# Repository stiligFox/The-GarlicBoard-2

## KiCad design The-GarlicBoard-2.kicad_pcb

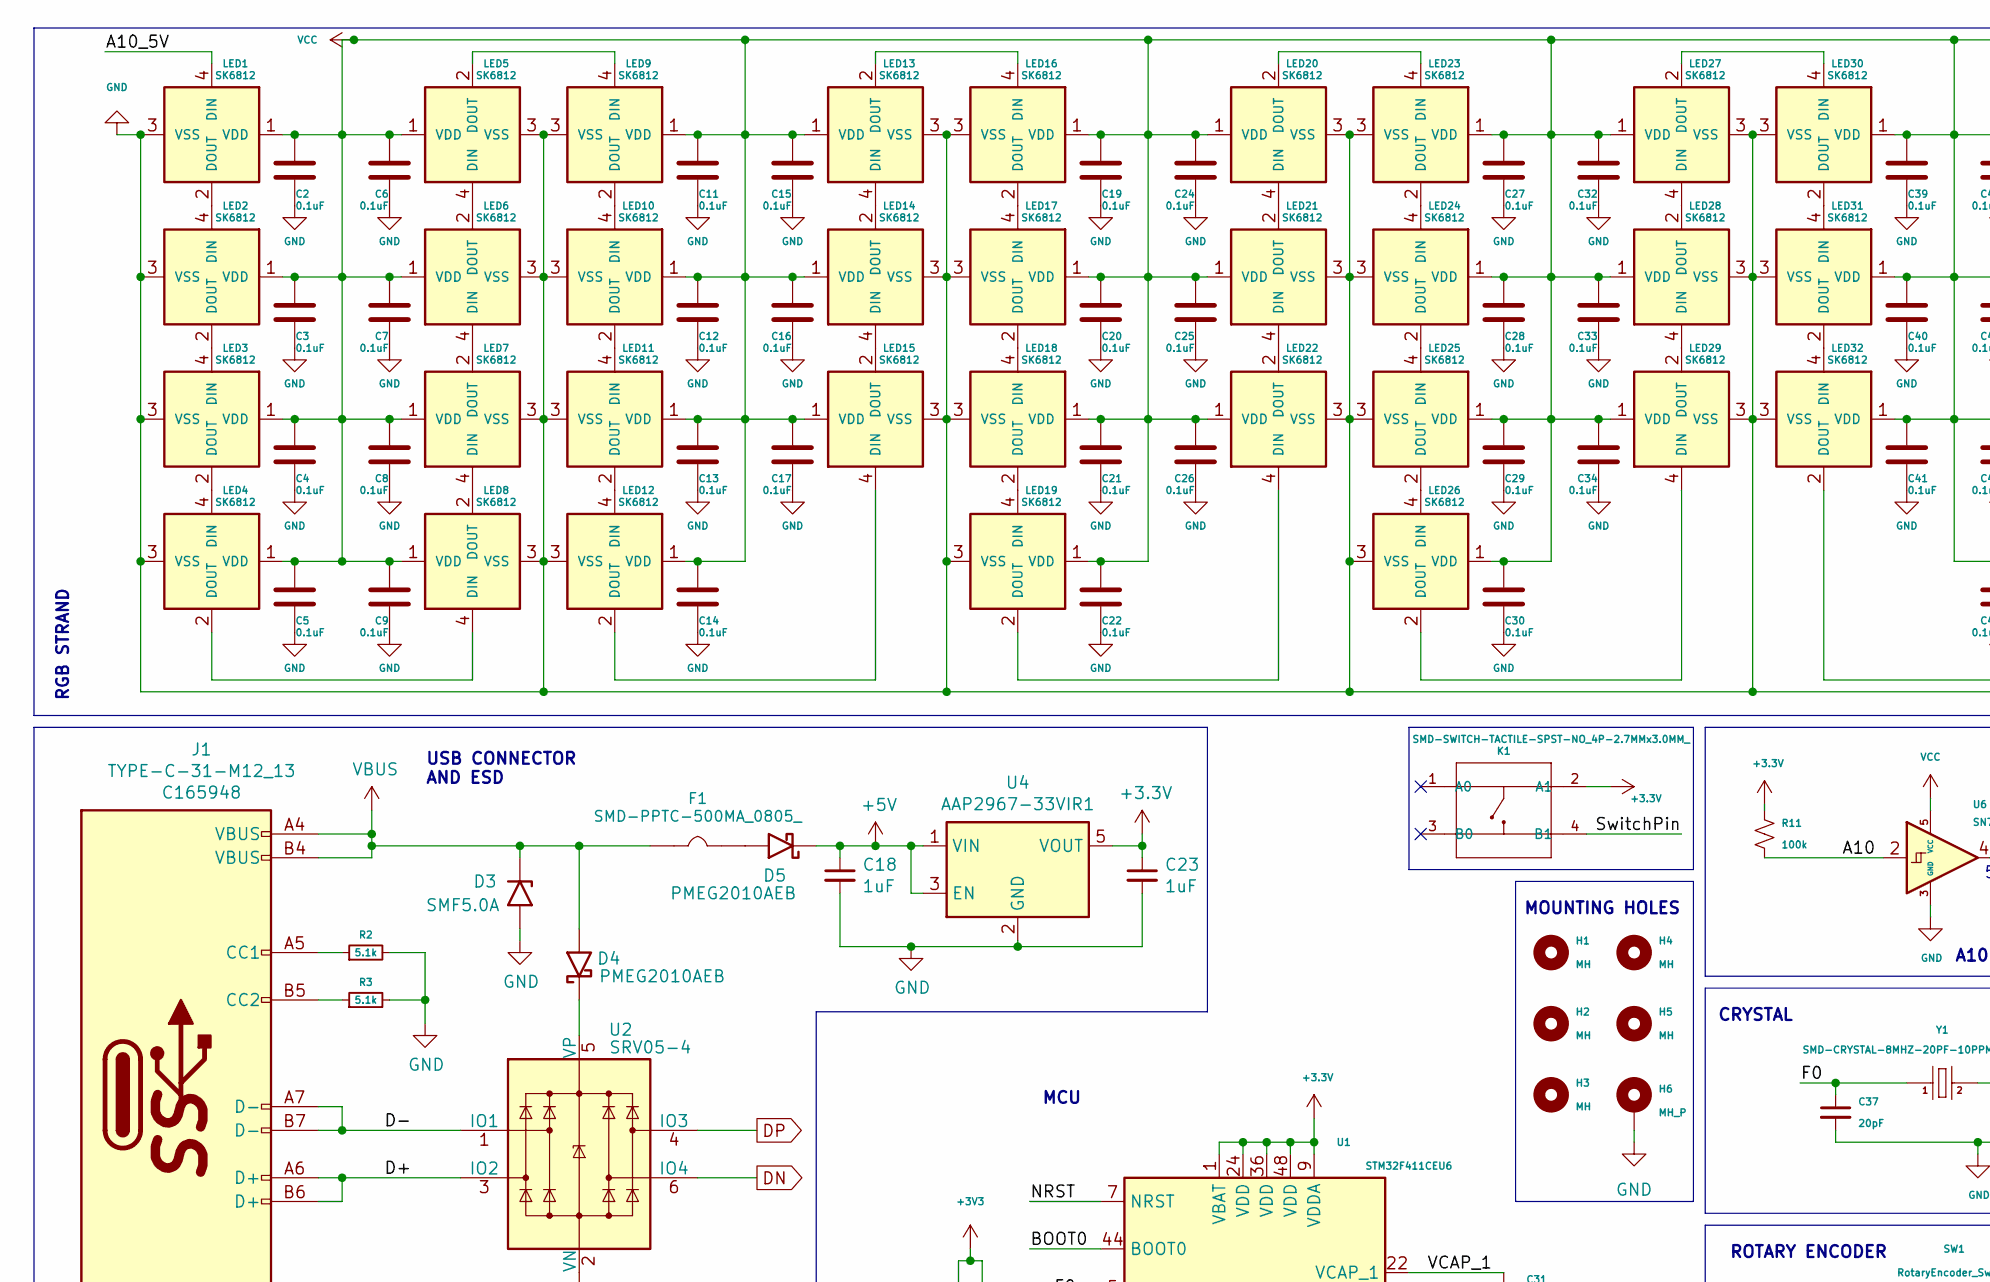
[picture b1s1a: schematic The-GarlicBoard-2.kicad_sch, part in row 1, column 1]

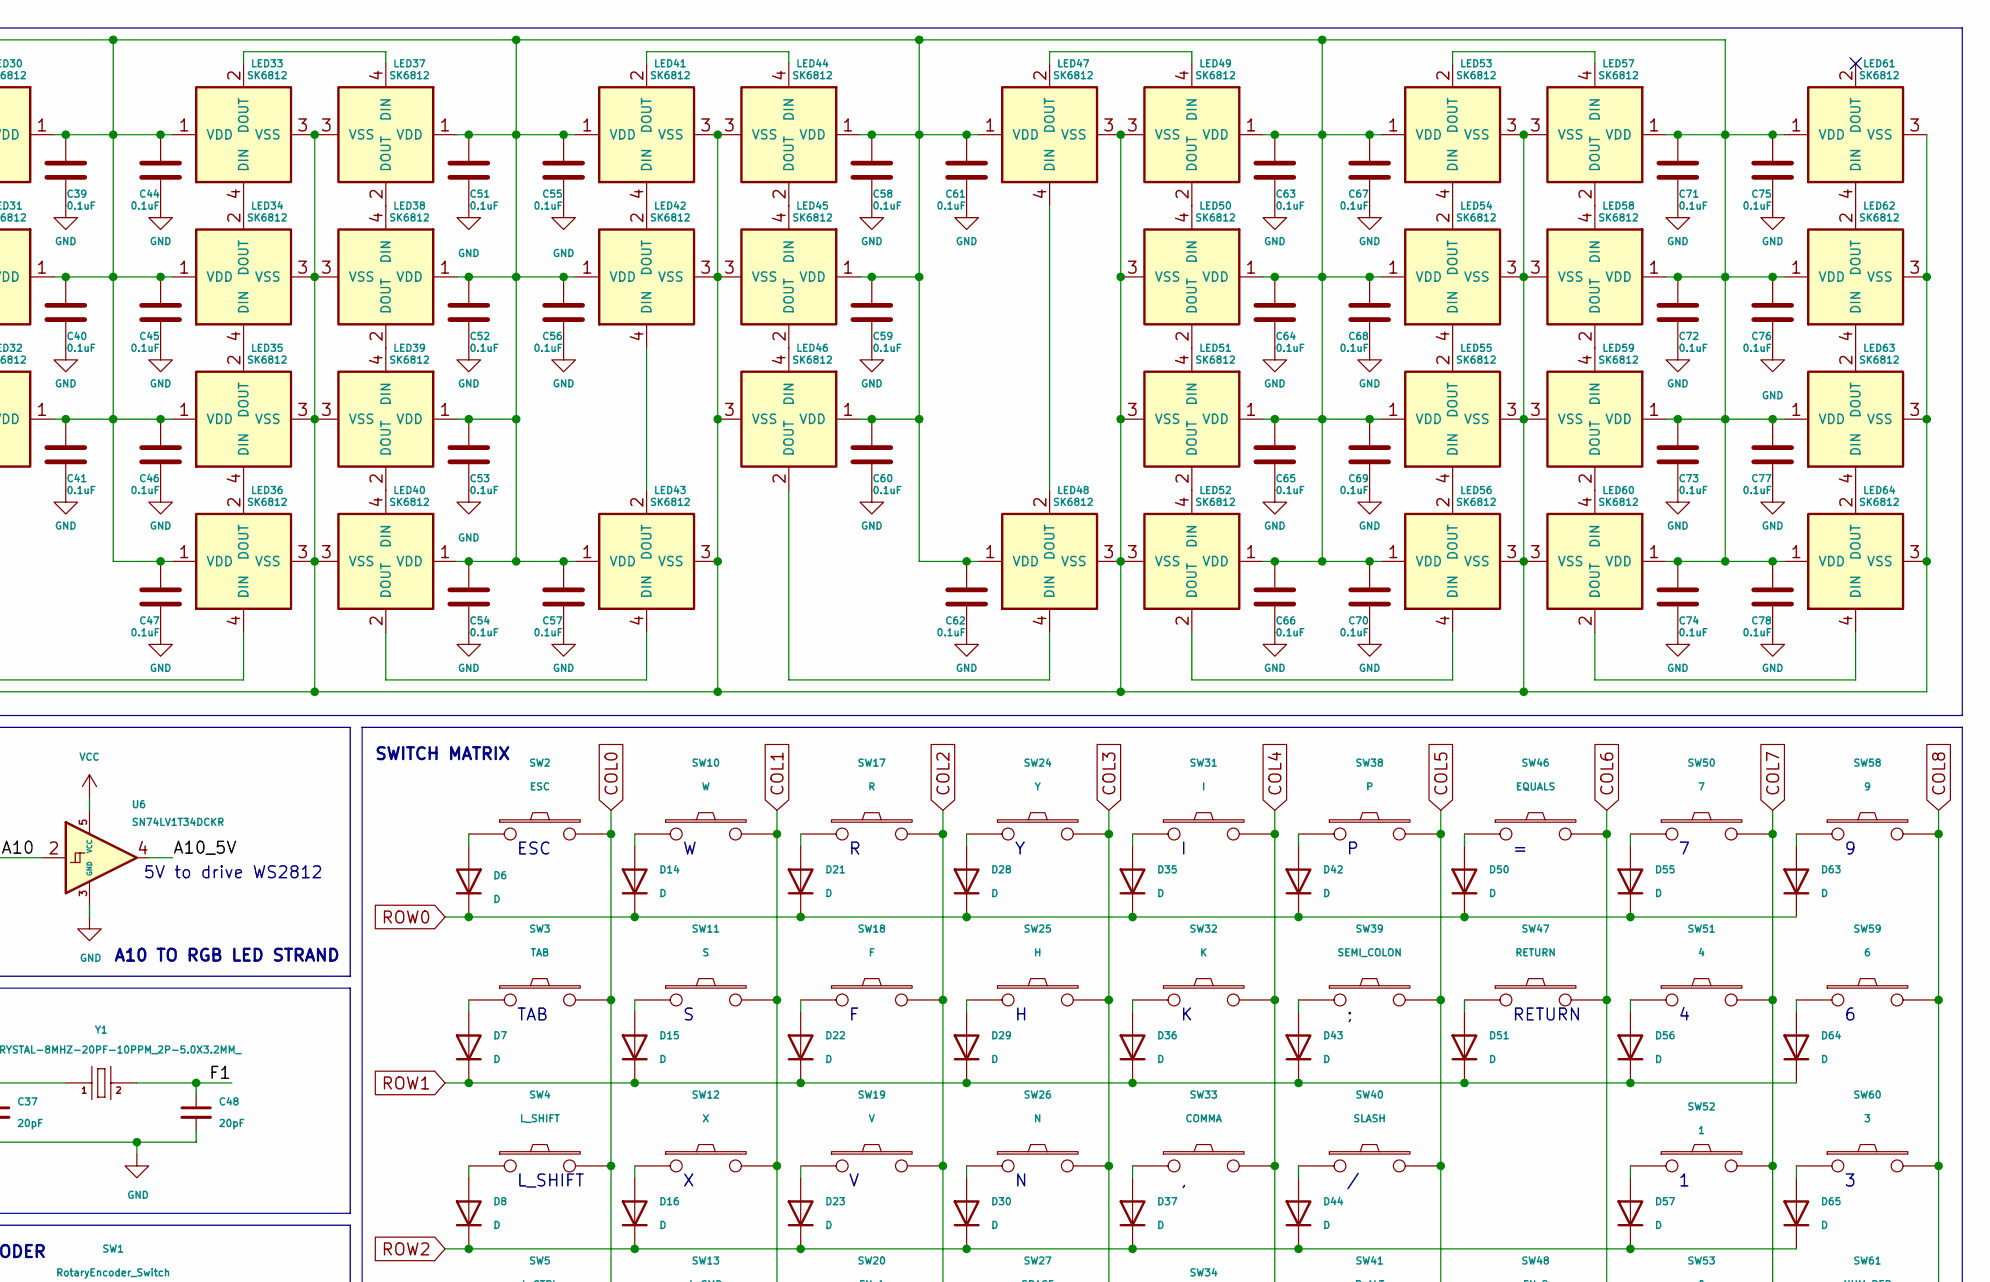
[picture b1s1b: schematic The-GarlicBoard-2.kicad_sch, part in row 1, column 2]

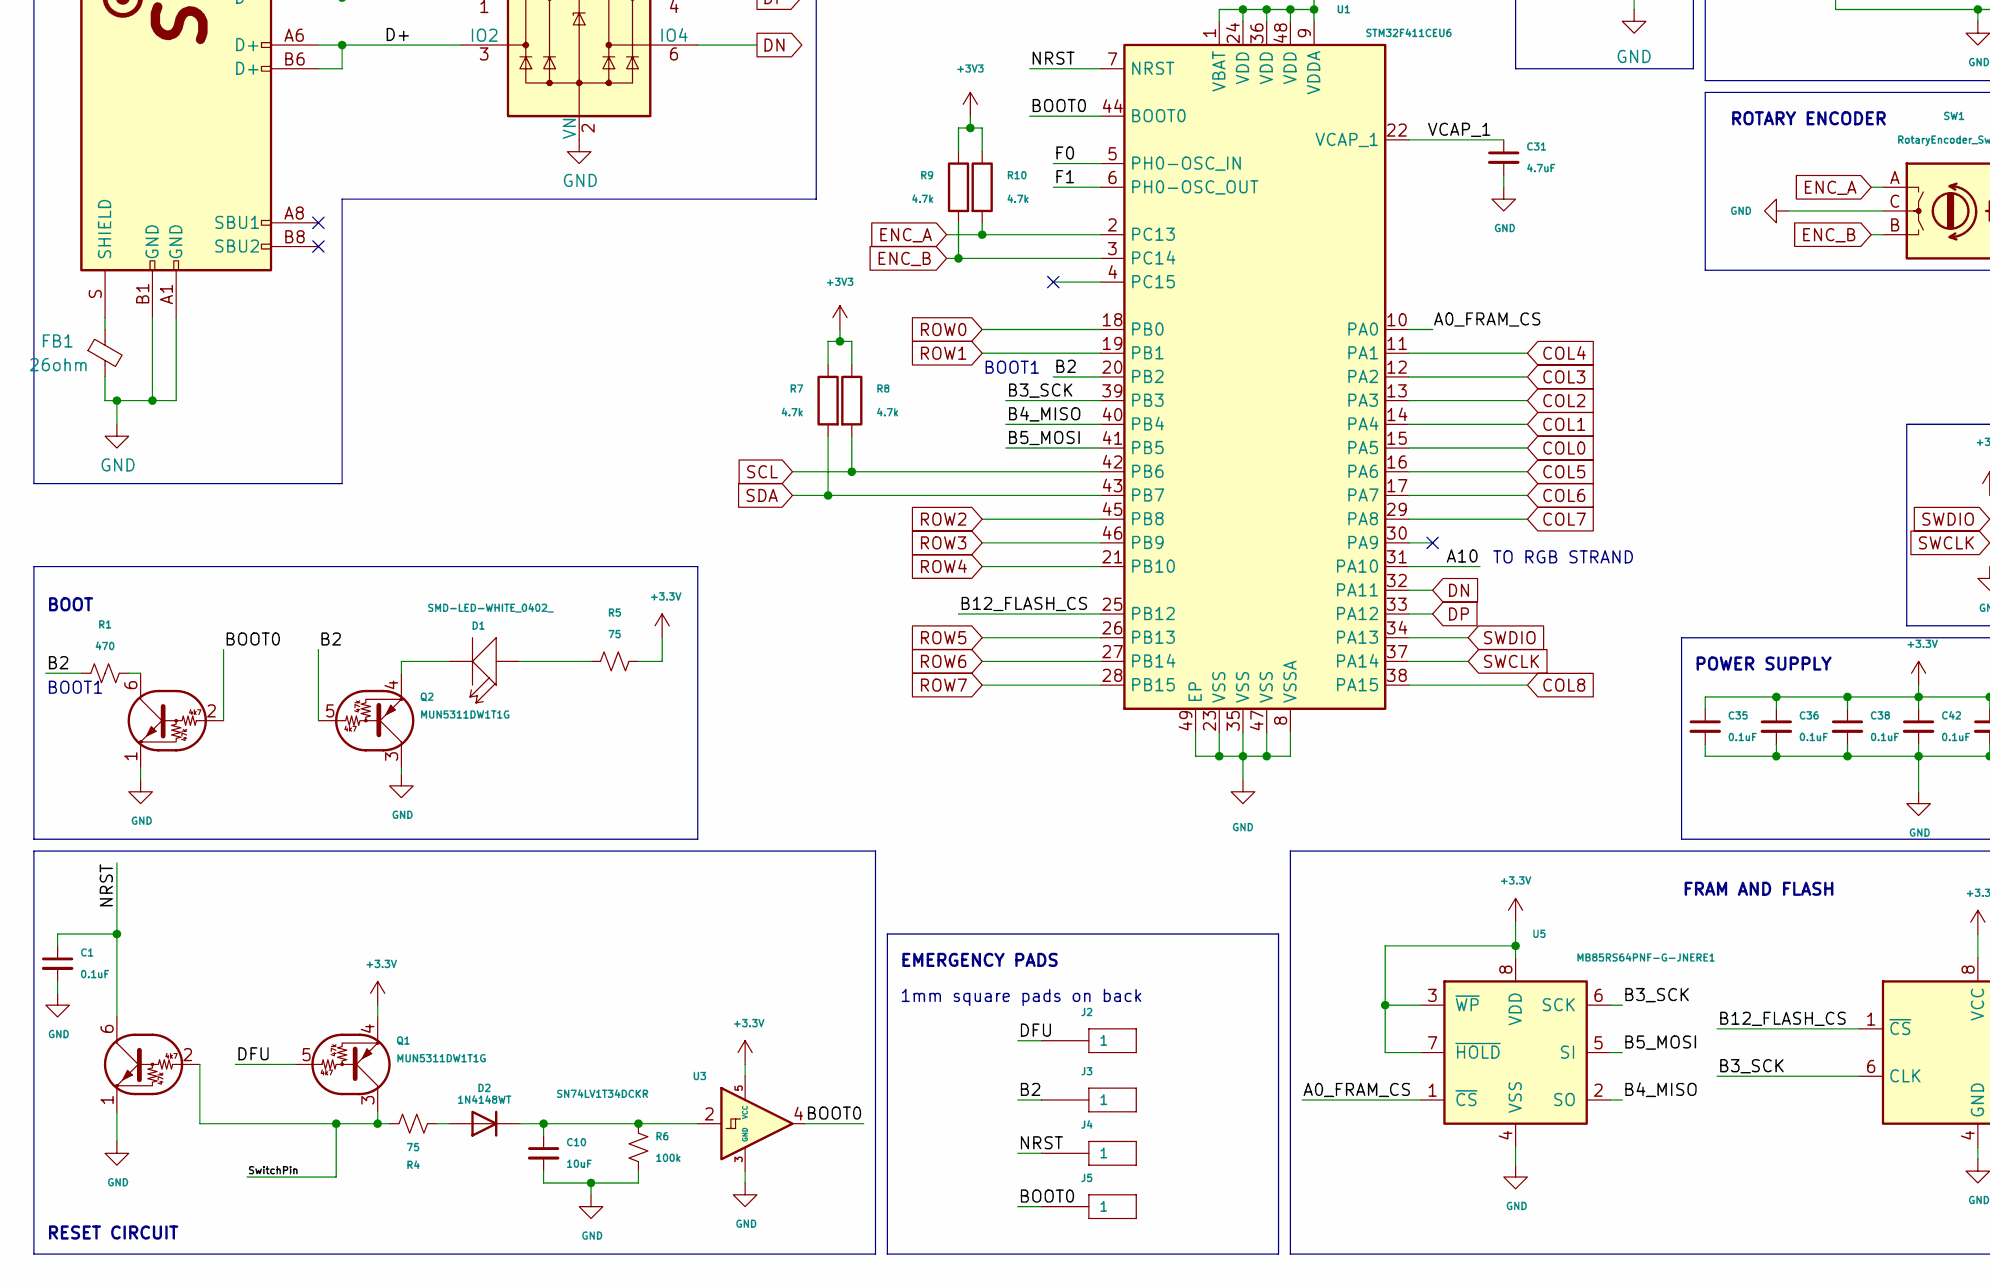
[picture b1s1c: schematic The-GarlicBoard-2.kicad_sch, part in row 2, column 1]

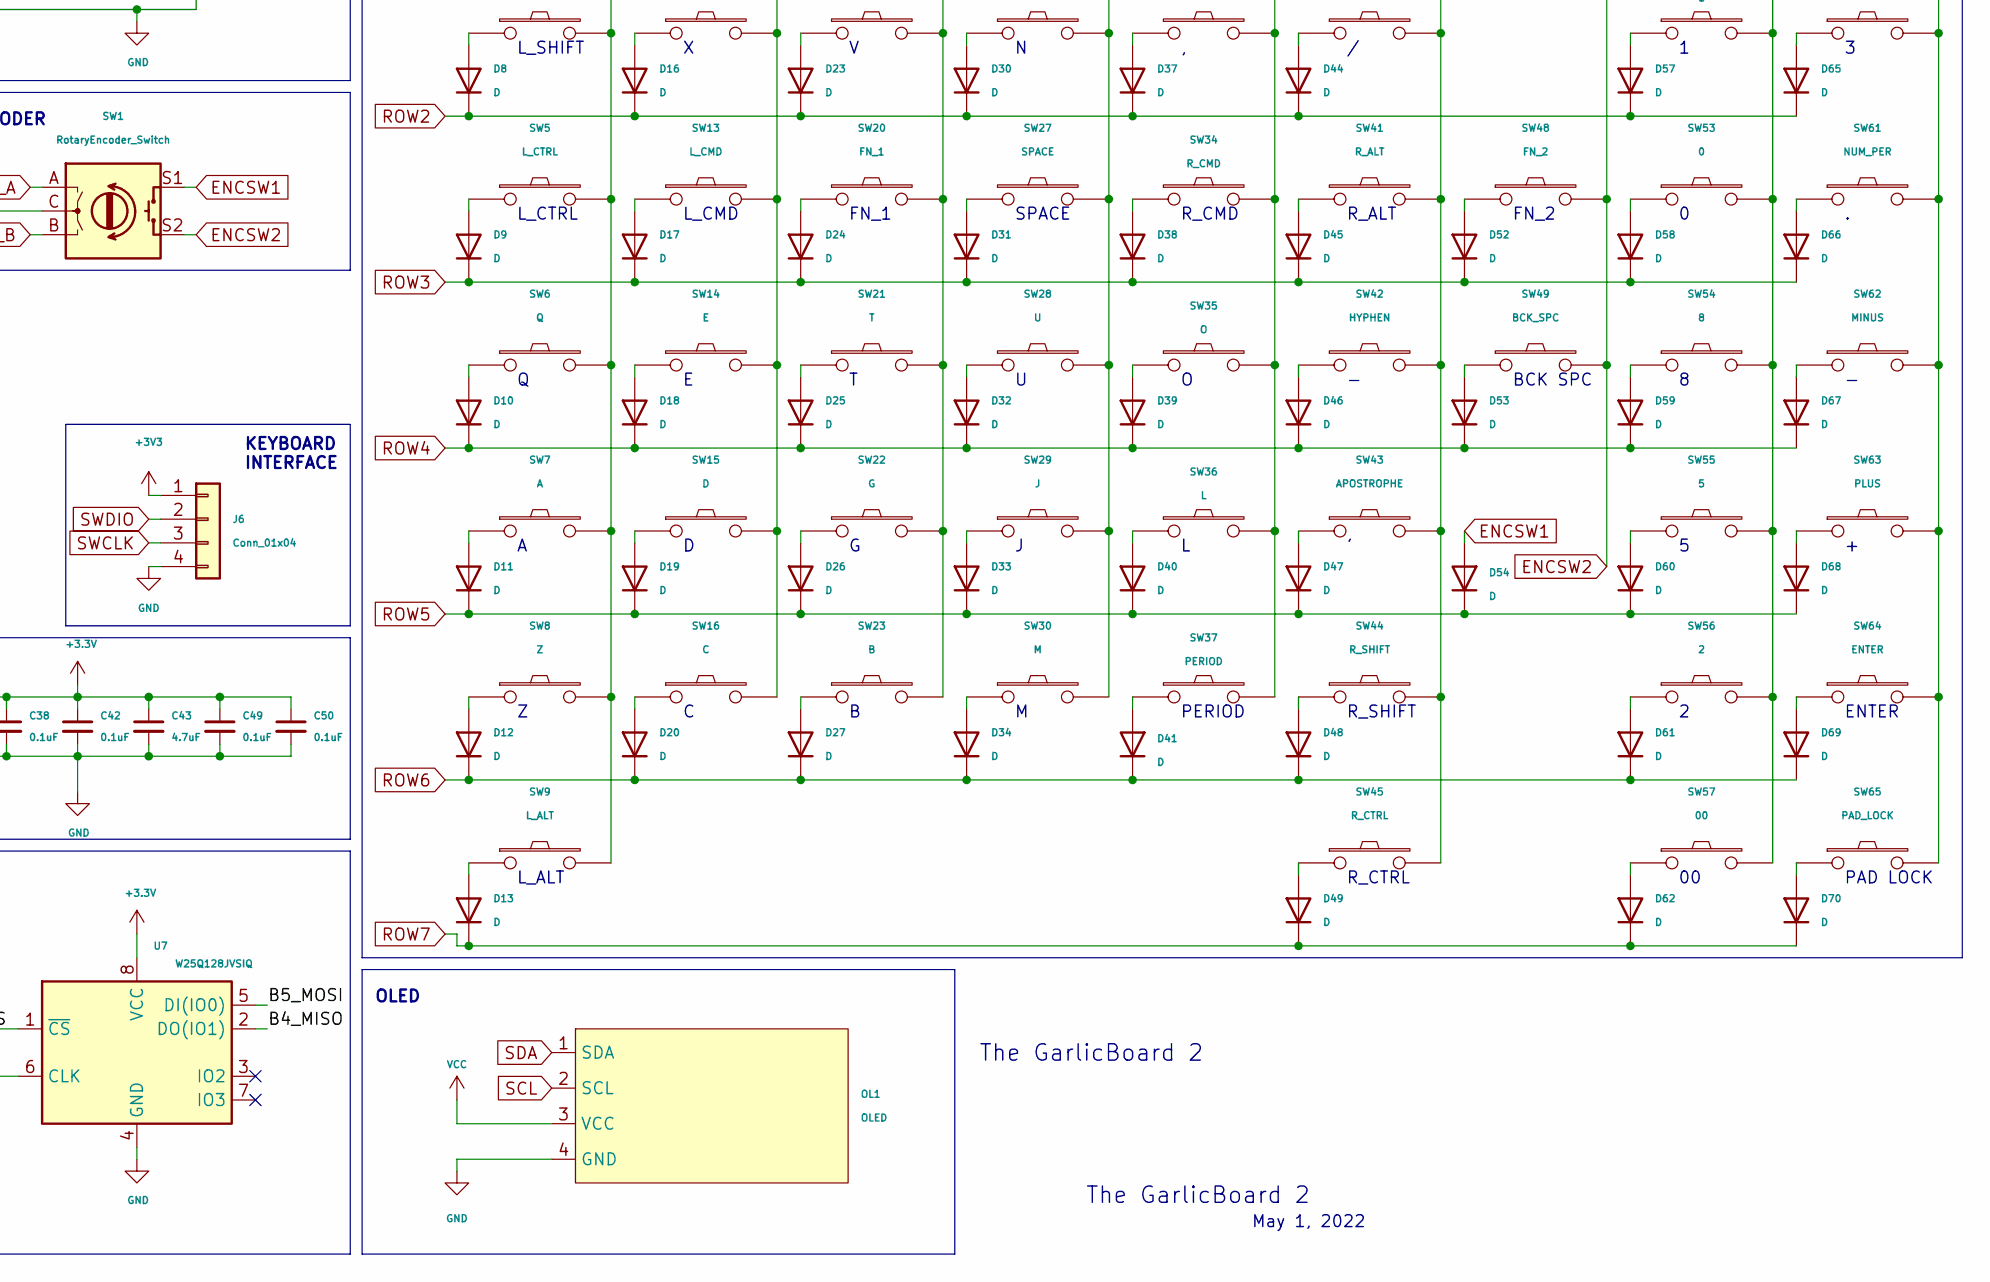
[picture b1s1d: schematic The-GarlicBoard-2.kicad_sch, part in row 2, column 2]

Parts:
C1, C35, C36, C38, C42, C49, C50: cap_100nF_16v_0402; C_0402_1005Metric; MPN CL05B104KO5NNNC; LCSC C1525
C2, C3, C4, C5, C6, C7, C8, C9, C11, C12, C13, C14, C15, C16, C17, C19, C20, C21, C22, C24, C25, C26, C27, C28, C29, C30, C32, C33, C34, C39, C40, C41, C44, C45, C46, C47, C51, C52, C53, C54, C55, C56, C57, C58, C59, C60, C61, C62, C63, C64, C65, C66, C67, C68, C69, C70, C71, C72, C73, C74, C75, C76, C77, C78: 0.1uF; C_0402_1005Metric
C10: cap_10uF_10v_0402; C_0402_1005Metric; MPN CL10A106KP8NNNC; LCSC C19702
C18, C23: cap_1uF_10v_0402; C_0402_1005Metric; MPN CC0402KRX5R6BB105; LCSC C52923
C31, C43: cap_4.7uF_10v_0402; C_0402_1005Metric; MPN CL05A475MP5NRNC; LCSC C23733
C37, C48: cap_20pF_50v_0402; C_0402_1005Metric; MPN 0402CG200J500NT; LCSC C1554
D1: SMD-LED-WHITE_0402_; LED_0402; MPN 16-219A/T2D-AR2T1QY/3T; LCSC C74342
D2: 1N4148WT; D_SOD-523
D3: SMF5.0A; D_SOD-123FL; LCSC C193402
D4, D5: PMEG2010AEB; D_SOD-523; LCSC C282563
D6, D7, D8, D9, D10, D11, D12, D13, D14, D15, D16, D17, D18, D19, D20, D21, D22, D23, D24, D25, D26, D27, D28, D29, D30, D31, D32, D33, D34, D35, D36, D37, D38, D39, D40, D41, D42, D43, D44, D45, D46, D47, D48, D49, D50, D51, D52, D53, D54, D55, D56, D57, D58, D59, D60, D61, D62, D63, D64, D65, D66, D67, D68, D69, D70: D; D_0402_1005Metric
F1: SMD-PPTC-500MA_0805_; F0805; MPN SMD0805-050; LCSC C66452
FB1: fb_0402_26ohm; R_0402_1005Metric; MPN CBG100505U260T; LCSC C668229
H1, H2, H3, H4, H5: MH; MountingHole_2.2mm_M2
H6: MH_P; MountingHole_2.2mm_M2_DIN965_Pad
J1: TYPE-C-31-M12_13; TYPE-C-31-M-12; MPN TYPE-C-31-M-12; LCSC C165948
J2, J3, J4, J5: PAD_SQUARE_1MM
J6: Conn_01x04; JST_XH_B4B-XH-A_1x04_P2.50mm_Vertical
K1: SMD-SWITCH-TACTILE-SPST-NO_4P-2.7MMx3.0MM_; SW4-SMD-2.7X3.0X1.4MM; MPN TBE-Q-T/R
LED1, LED2, LED3, LED4, LED5, LED6, LED7, LED8, LED9, LED10, LED11, LED12, LED13, LED14, LED15, LED16, LED17, LED18, LED19, LED20, LED21, LED22, LED23, LED24, LED25, LED26, LED27, LED28, LED29, LED30, LED31, LED32, LED33, LED34, LED35, LED36, LED37, LED38, LED39, LED40, LED41, LED42, LED43, LED44, LED45, LED46, LED47, LED48, LED49, LED50, LED51, LED52, LED53, LED54, LED55, LED56, LED57, LED58, LED59, LED60, LED61, LED62, LED63, LED64: SK6812; SK6812-MINI-E
OL1: OLED; OLED_v2
Q1, Q2: MUN5311DW1T1G; SOT-363_SC-70-6_SC-88; LCSC C152542
R1: r_470_0402_1p; R_0402_1005Metric; MPN 0402WGF4700TCE; LCSC C25117
R2, R3: 5.1k; R_0402
R4, R5: r_75_0402_1p; R_0402_1005Metric; MPN 0402WGF750JTCE; LCSC C25133
R6, R11: r_100k_0402_1p; R_0402_1005Metric; MPN 0402WGF1003TCE; LCSC C25741
R7, R8, R9, R10: 4.7k; R_0402_1005Metric
SW1: RotaryEncoder_Switch; RotaryEncoder_EC11
SW2: ESC; MX-Hotswap-1U
SW3: TAB; MX-Hotswap-1.25U
SW4: L_SHIFT; MX-Hotswap-1.75U
SW5: L_CTRL; MX-Hotswap-1.25U
SW6: Q; MX-Hotswap-1U
SW7: A; MX-Hotswap-1U
SW8: Z; MX-Hotswap-1U
SW9: L_ALT; MX-Hotswap-1.25U
SW10: W; MX-Hotswap-1U
SW11: S; MX-Hotswap-1U
SW12: X; MX-Hotswap-1U
SW13: L_CMD; MX-Hotswap-1.25U
SW14: E; MX-Hotswap-1U
SW15: D; MX-Hotswap-1U
SW16: C; MX-Hotswap-1U
SW17: R; MX-Hotswap-1U
SW18: F; MX-Hotswap-1U
SW19: V; MX-Hotswap-1U
SW20: FN_1; MX-Hotswap-2.75U
SW21: T; MX-Hotswap-1U
SW22: G; MX-Hotswap-1U
SW23: B; MX-Hotswap-1U
SW24: Y; MX-Hotswap-1U
SW25: H; MX-Hotswap-1U
SW26: N; MX-Hotswap-1U
SW27: SPACE; MX-Hotswap-2.75U
SW28: U; MX-Hotswap-1U
SW29: J; MX-Hotswap-1U
SW30: M; MX-Hotswap-1U
SW31: I; MX-Hotswap-1U
SW32: K; MX-Hotswap-1U
SW33: COMMA; MX-Hotswap-1U
SW34: R_CMD; MX-Hotswap-1.25U
SW35: O; MX-Hotswap-1U
SW36: L; MX-Hotswap-1U
SW37: PERIOD; MX-Hotswap-1U
SW38: P; MX-Hotswap-1U
SW39: SEMI_COLON; MX-Hotswap-1U
SW40: SLASH; MX-Hotswap-1U
SW41: R_ALT; MX-Hotswap-1.25U
SW42: HYPHEN; MX-Hotswap-1U
SW43: APOSTROPHE; MX-Hotswap-1U
SW44: R_SHIFT; MX-Hotswap-2.25U
SW45: R_CTRL; MX-Hotswap-1.25U
SW46: EQUALS; MX-Hotswap-1U
SW47: RETURN; MX-Hotswap-1.75U
SW48: FN_2; MX-Hotswap-1U
SW49: BCK_SPC; MX-Hotswap-1U
SW50: 7; MX-Hotswap-1U
SW51: 4; MX-Hotswap-1U
SW52: 1; MX-Hotswap-1U
SW53: 0; MX-Hotswap-1U
SW54: 8; MX-Hotswap-1U
SW55: 5; MX-Hotswap-1U
SW56: 2; MX-Hotswap-1U
SW57: 00; MX-Hotswap-1U
SW58: 9; MX-Hotswap-1U
SW59: 6; MX-Hotswap-1U
SW60: 3; MX-Hotswap-1U
SW61: NUM_PER; MX-Hotswap-1U
SW62: MINUS; MX-Hotswap-1U
SW63: PLUS; MX-Hotswap-1U
SW64: ENTER; MX-Hotswap-1U
SW65: PAD_LOCK; MX-Hotswap-1U
U1: STM32F411CEU6; QFN-48-1EP_7x7mm_P0.5mm_EP5.6x5.6mm_ThermalVias
U2: SRV05-4; SOT-23-6; LCSC C85364
U3, U6: SN74LV1T34DCKR; SOT-353_SC-70-5; LCSC C78541
U4: AAP2967-33VIR1; SOT-23-5; LCSC C370742
U5: MB85RS64PNF-G-JNERE1; SOP-8_3.9x4.9mm_P1.27mm; LCSC C8741
U7: W25Q128JVSIQ; SOIC-8_5.23x5.23mm_P1.27mm; LCSC C97521
Y1: SMD-CRYSTAL-8MHZ-20PF-10PPM_2P-5.0X3.2MM_; X2-SMD-5.0X3.2X1.3MM; MPN X50328MSB2GI; LCSC C115962

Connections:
+3.3V: C23.1, C35.1, C36.1, C38.1, C42.1, C43.1, C49.1, C50.1, K1.2 (A1), Q1.4 (E), R5.1, R11.1, U1.1 (VBAT), U1.9 (VDDA), U1.24 (VDD), U1.36 (VDD), U1.48 (VDD), U3.5 (VCC), U4.5 (VOUT), U5.3 (~WP), U5.7 (~HOLD), U5.8 (VDD), U7.8 (VCC)
+3V3: J6.1, R7.1, R8.1, R9.1, R10.1
+5V: C18.1, D5.1 (K), U4.1 (VIN), U4.3 (EN)
/A0_FRAM_CS: U1.10 (PA0), U5.1 (~CS)
/A10: R11.2, U1.31 (PA10), U6.2
/A10_5V: LED1.4 (DIN), U6.4
/B2: J3.1, Q2.5, R1.2, U1.20 (PB2)
/B3_SCK: U1.39 (PB3), U5.6 (SCK), U7.6 (CLK)
/B4_MISO: U1.40 (PB4), U5.2 (SO), U7.2 (DO(IO1))
/B5_MOSI: U1.41 (PB5), U5.5 (SI), U7.5 (DI(IO0))
/B12_FLASH_CS: U1.25 (PB12), U7.1 (~CS)
/BOOT0: J5.1, Q2.2 (B), U1.44 (BOOT0), U3.4
/D+: J1.A6 (D+), J1.B6 (D+), U2.3 (IO2)
/D-: J1.A7 (D-), J1.B7 (D-), U2.1 (IO1)
/DFU: J2.1, Q1.5
/F0: C37.1, U1.5 (PH0-OSC_IN), Y1.1
/F1: C48.1, U1.6 (PH0-OSC_OUT), Y1.2
/NRST: C1.1, J4.1, Q1.6 (C), U1.7 (NRST)
/SwitchPin: K1.4 (B1), Q1.2 (B), Q1.3 (C), R4.1
/VCAP_1: C31.1, U1.22 (VCAP_1)
COL0: SW2.2, SW3.2, SW4.2, SW5.2, SW6.2, SW7.2, SW8.2, SW9.2, U1.15 (PA5)
COL1: SW10.2, SW11.2, SW12.2, SW13.2, SW14.2, SW15.2, SW16.2, U1.14 (PA4)
COL2: SW17.2, SW18.2, SW19.2, SW20.2, SW21.2, SW22.2, SW23.2, U1.13 (PA3)
COL3: SW24.2, SW25.2, SW26.2, SW27.2, SW28.2, SW29.2, SW30.2, U1.12 (PA2)
COL4: SW31.2, SW32.2, SW33.2, SW34.2, SW35.2, SW36.2, SW37.2, U1.11 (PA1)
COL5: SW38.2, SW39.2, SW40.2, SW41.2, SW42.2, SW43.2, SW44.2, SW45.2, U1.16 (PA6)
COL6: SW1.S2, SW46.2, SW47.2, SW48.2, SW49.2, U1.17 (PA7)
COL7: SW50.2, SW51.2, SW52.2, SW53.2, SW54.2, SW55.2, SW56.2, SW57.2, U1.29 (PA8)
COL8: SW58.2, SW59.2, SW60.2, SW61.2, SW62.2, SW63.2, SW64.2, SW65.2, U1.38 (PA15)
DN: U1.32 (PA11), U2.6 (IO4)
DP: U1.33 (PA12), U2.4 (IO3)
ENCSW1: D54.2 (A), SW1.S1
ENC_A: R10.2, SW1.A, U1.2 (PC13)
ENC_B: R9.2, SW1.B, U1.3 (PC14)
GND: C1.2, C2.2, C3.2, C4.2, C5.2, C6.2, C7.2, C8.2, C9.2, C10.2, C11.2, C12.2, C13.2, C14.2, C15.2, C16.2, C17.2, C18.2, C19.2, C20.2, C21.2, C22.2, C23.2, C24.2, C25.2, C26.2, C27.2, C28.2, C29.2, C30.2, C31.2, C32.2, C33.2, C34.2, C35.2, C36.2, C37.2, C38.2, C39.2, C40.2, C41.2, C42.2, C43.2, C44.2, C45.2, C46.2, C47.2, C48.2, C49.2, C50.2, C51.2, C52.2, C53.2, C54.2, C55.2, C56.2, C57.2, C58.2, C59.2, C60.2, C61.2, C62.2, C63.2, C64.2, C65.2, C66.2, C67.2, C68.2, C69.2, C70.2, C71.2, C72.2, C73.2, C74.2, C75.2, C76.2, C77.2, C78.2, D3.2 (A2), FB1.2, H6.1, J1.A1 (GND), J1.B1 (GND), J6.4, LED1.3 (VSS), LED2.3 (VSS), LED3.3 (VSS), LED4.3 (VSS), LED5.3 (VSS), LED6.3 (VSS), LED7.3 (VSS), LED8.3 (VSS), LED9.3 (VSS), LED10.3 (VSS), LED11.3 (VSS), LED12.3 (VSS), LED13.3 (VSS), LED14.3 (VSS), LED15.3 (VSS), LED16.3 (VSS), LED17.3 (VSS), LED18.3 (VSS), LED19.3 (VSS), LED20.3 (VSS), LED21.3 (VSS), LED22.3 (VSS), LED23.3 (VSS), LED24.3 (VSS), LED25.3 (VSS), LED26.3 (VSS), LED27.3 (VSS), LED28.3 (VSS), LED29.3 (VSS), LED30.3 (VSS), LED31.3 (VSS), LED32.3 (VSS), LED33.3 (VSS), LED34.3 (VSS), LED35.3 (VSS), LED36.3 (VSS), LED37.3 (VSS), LED38.3 (VSS), LED39.3 (VSS), LED40.3 (VSS), LED41.3 (VSS), LED42.3 (VSS), LED43.3 (VSS), LED44.3 (VSS), LED45.3 (VSS), LED46.3 (VSS), LED47.3 (VSS), LED48.3 (VSS), LED49.3 (VSS), LED50.3 (VSS), LED51.3 (VSS), LED52.3 (VSS), LED53.3 (VSS), LED54.3 (VSS), LED55.3 (VSS), LED56.3 (VSS), LED57.3 (VSS), LED58.3 (VSS), LED59.3 (VSS), LED60.3 (VSS), LED61.3 (VSS), LED62.3 (VSS), LED63.3 (VSS), LED64.3 (VSS), OL1.4 (GND), Q1.1 (E), Q2.1 (E), Q2.3 (C), R2.2, R3.2, R6.2, SW1.C, U1.8 (VSSA), U1.23 (VSS), U1.35 (VSS), U1.47 (VSS), U1.49 (EP), U2.2 (VN), U3.3 (GND), U4.2 (GND), U5.4 (VSS), U6.3 (GND), U7.4 (GND)
unnamed: C10.1, D2.1 (K), R6.1, U3.2
unnamed: D1.+, R5.2
unnamed: D1.-, Q2.4 (E)
unnamed: D2.2 (A), R4.2
unnamed: D4.1 (K), U2.5 (VP)
unnamed: D5.2 (A), F1.1
unnamed: D6.2 (A), SW2.1
unnamed: D7.2 (A), SW3.1
unnamed: D8.2 (A), SW4.1
unnamed: D9.2 (A), SW5.1
unnamed: D10.2 (A), SW6.1
unnamed: D11.2 (A), SW7.1
unnamed: D12.2 (A), SW8.1
unnamed: D13.2 (A), SW9.1
unnamed: D14.2 (A), SW10.1
unnamed: D15.2 (A), SW11.1
unnamed: D16.2 (A), SW12.1
unnamed: D17.2 (A), SW13.1
unnamed: D18.2 (A), SW14.1
unnamed: D19.2 (A), SW15.1
unnamed: D20.2 (A), SW16.1
unnamed: D21.2 (A), SW17.1
unnamed: D22.2 (A), SW18.1
unnamed: D23.2 (A), SW19.1
unnamed: D24.2 (A), SW20.1
unnamed: D25.2 (A), SW21.1
unnamed: D26.2 (A), SW22.1
unnamed: D27.2 (A), SW23.1
unnamed: D28.2 (A), SW24.1
unnamed: D29.2 (A), SW25.1
unnamed: D30.2 (A), SW26.1
unnamed: D31.2 (A), SW27.1
unnamed: D32.2 (A), SW28.1
unnamed: D33.2 (A), SW29.1
unnamed: D34.2 (A), SW30.1
unnamed: D35.2 (A), SW31.1
unnamed: D36.2 (A), SW32.1
unnamed: D37.2 (A), SW33.1
unnamed: D38.2 (A), SW34.1
unnamed: D39.2 (A), SW35.1
unnamed: D40.2 (A), SW36.1
unnamed: D41.2 (A), SW37.1
unnamed: D42.2 (A), SW38.1
unnamed: D43.2 (A), SW39.1
unnamed: D44.2 (A), SW40.1
unnamed: D45.2 (A), SW41.1
unnamed: D46.2 (A), SW42.1
unnamed: D47.2 (A), SW43.1
unnamed: D48.2 (A), SW44.1
unnamed: D49.2 (A), SW45.1
unnamed: D50.2 (A), SW46.1
unnamed: D51.2 (A), SW47.1
unnamed: D52.2 (A), SW48.1
unnamed: D53.2 (A), SW49.1
unnamed: D55.2 (A), SW50.1
unnamed: D56.2 (A), SW51.1
unnamed: D57.2 (A), SW52.1
unnamed: D58.2 (A), SW53.1
unnamed: D59.2 (A), SW54.1
unnamed: D60.2 (A), SW55.1
unnamed: D61.2 (A), SW56.1
unnamed: D62.2 (A), SW57.1
unnamed: D63.2 (A), SW58.1
unnamed: D64.2 (A), SW59.1
unnamed: D65.2 (A), SW60.1
unnamed: D66.2 (A), SW61.1
unnamed: D67.2 (A), SW62.1
unnamed: D68.2 (A), SW63.1
unnamed: D69.2 (A), SW64.1
unnamed: D70.2 (A), SW65.1
unnamed: FB1.1, J1.S (SHIELD)
unnamed: J1.A5 (CC1), R2.1
unnamed: J1.B5 (CC2), R3.1
unnamed: LED1.2 (DOUT), LED2.4 (DIN)
unnamed: LED2.2 (DOUT), LED3.4 (DIN)
unnamed: LED3.2 (DOUT), LED4.4 (DIN)
unnamed: LED4.2 (DOUT), LED8.4 (DIN)
unnamed: LED5.2 (DOUT), LED9.4 (DIN)
unnamed: LED5.4 (DIN), LED6.2 (DOUT)
unnamed: LED6.4 (DIN), LED7.2 (DOUT)
unnamed: LED7.4 (DIN), LED8.2 (DOUT)
unnamed: LED10.2 (DOUT), LED11.4 (DIN)
unnamed: LED9.2 (DOUT), LED10.4 (DIN)
unnamed: LED11.2 (DOUT), LED12.4 (DIN)
unnamed: LED12.2 (DOUT), LED15.4 (DIN)
unnamed: LED13.2 (DOUT), LED16.4 (DIN)
unnamed: LED13.4 (DIN), LED14.2 (DOUT)
unnamed: LED14.4 (DIN), LED15.2 (DOUT)
unnamed: LED16.2 (DOUT), LED17.4 (DIN)
unnamed: LED17.2 (DOUT), LED18.4 (DIN)
unnamed: LED18.2 (DOUT), LED19.4 (DIN)
unnamed: LED19.2 (DOUT), LED22.4 (DIN)
unnamed: LED20.2 (DOUT), LED23.4 (DIN)
unnamed: LED20.4 (DIN), LED21.2 (DOUT)
unnamed: LED21.4 (DIN), LED22.2 (DOUT)
unnamed: LED23.2 (DOUT), LED24.4 (DIN)
unnamed: LED24.2 (DOUT), LED25.4 (DIN)
unnamed: LED25.2 (DOUT), LED26.4 (DIN)
unnamed: LED26.2 (DOUT), LED29.4 (DIN)
unnamed: LED27.2 (DOUT), LED30.4 (DIN)
unnamed: LED27.4 (DIN), LED28.2 (DOUT)
unnamed: LED28.4 (DIN), LED29.2 (DOUT)
unnamed: LED30.2 (DOUT), LED31.4 (DIN)
unnamed: LED31.2 (DOUT), LED32.4 (DIN)
unnamed: LED32.2 (DOUT), LED36.4 (DIN)
unnamed: LED33.2 (DOUT), LED37.4 (DIN)
unnamed: LED33.4 (DIN), LED34.2 (DOUT)
unnamed: LED34.4 (DIN), LED35.2 (DOUT)
unnamed: LED35.4 (DIN), LED36.2 (DOUT)
unnamed: LED37.2 (DOUT), LED38.4 (DIN)
unnamed: LED38.2 (DOUT), LED39.4 (DIN)
unnamed: LED39.2 (DOUT), LED40.4 (DIN)
unnamed: LED40.2 (DOUT), LED43.4 (DIN)
unnamed: LED41.2 (DOUT), LED44.4 (DIN)
unnamed: LED41.4 (DIN), LED42.2 (DOUT)
unnamed: LED42.4 (DIN), LED43.2 (DOUT)
unnamed: LED44.2 (DOUT), LED45.4 (DIN)
unnamed: LED45.2 (DOUT), LED46.4 (DIN)
unnamed: LED46.2 (DOUT), LED48.4 (DIN)
unnamed: LED47.2 (DOUT), LED49.4 (DIN)
unnamed: LED47.4 (DIN), LED48.2 (DOUT)
unnamed: LED49.2 (DOUT), LED50.4 (DIN)
unnamed: LED50.2 (DOUT), LED51.4 (DIN)
unnamed: LED51.2 (DOUT), LED52.4 (DIN)
unnamed: LED52.2 (DOUT), LED56.4 (DIN)
unnamed: LED53.2 (DOUT), LED57.4 (DIN)
unnamed: LED53.4 (DIN), LED54.2 (DOUT)
unnamed: LED54.4 (DIN), LED55.2 (DOUT)
unnamed: LED55.4 (DIN), LED56.2 (DOUT)
unnamed: LED57.2 (DOUT), LED58.4 (DIN)
unnamed: LED58.2 (DOUT), LED59.4 (DIN)
unnamed: LED59.2 (DOUT), LED60.4 (DIN)
unnamed: LED60.2 (DOUT), LED64.4 (DIN)
unnamed: LED61.4 (DIN), LED62.2 (DOUT)
unnamed: LED62.4 (DIN), LED63.2 (DOUT)
unnamed: LED63.4 (DIN), LED64.2 (DOUT)
unnamed: Q2.6 (C), R1.1
ROW0: D6.1 (K), D14.1 (K), D21.1 (K), D28.1 (K), D35.1 (K), D42.1 (K), D50.1 (K), D55.1 (K), D63.1 (K), U1.18 (PB0)
ROW1: D7.1 (K), D15.1 (K), D22.1 (K), D29.1 (K), D36.1 (K), D43.1 (K), D51.1 (K), D56.1 (K), D64.1 (K), U1.19 (PB1)
ROW2: D8.1 (K), D16.1 (K), D23.1 (K), D30.1 (K), D37.1 (K), D44.1 (K), D57.1 (K), D65.1 (K), U1.45 (PB8)
ROW3: D9.1 (K), D17.1 (K), D24.1 (K), D31.1 (K), D38.1 (K), D45.1 (K), D52.1 (K), D58.1 (K), D66.1 (K), U1.46 (PB9)
ROW4: D10.1 (K), D18.1 (K), D25.1 (K), D32.1 (K), D39.1 (K), D46.1 (K), D53.1 (K), D59.1 (K), D67.1 (K), U1.21 (PB10)
ROW5: D11.1 (K), D19.1 (K), D26.1 (K), D33.1 (K), D40.1 (K), D47.1 (K), D54.1 (K), D60.1 (K), D68.1 (K), U1.26 (PB13)
ROW6: D12.1 (K), D20.1 (K), D27.1 (K), D34.1 (K), D41.1 (K), D48.1 (K), D61.1 (K), D69.1 (K), U1.27 (PB14)
ROW7: D13.1 (K), D49.1 (K), D62.1 (K), D70.1 (K), U1.28 (PB15)
SCL: OL1.2 (SCL), R8.2, U1.42 (PB6)
SDA: OL1.1 (SDA), R7.2, U1.43 (PB7)
SWCLK: J6.3, U1.37 (PA14)
SWDIO: J6.2, U1.34 (PA13)
VBUS: D3.1 (A1), D4.2 (A), F1.2, J1.A4 (VBUS), J1.B4 (VBUS)
VCC: C2.1, C3.1, C4.1, C5.1, C6.1, C7.1, C8.1, C9.1, C11.1, C12.1, C13.1, C14.1, C15.1, C16.1, C17.1, C19.1, C20.1, C21.1, C22.1, C24.1, C25.1, C26.1, C27.1, C28.1, C29.1, C30.1, C32.1, C33.1, C34.1, C39.1, C40.1, C41.1, C44.1, C45.1, C46.1, C47.1, C51.1, C52.1, C53.1, C54.1, C55.1, C56.1, C57.1, C58.1, C59.1, C60.1, C61.1, C62.1, C63.1, C64.1, C65.1, C66.1, C67.1, C68.1, C69.1, C70.1, C71.1, C72.1, C73.1, C74.1, C75.1, C76.1, C77.1, C78.1, LED1.1 (VDD), LED2.1 (VDD), LED3.1 (VDD), LED4.1 (VDD), LED5.1 (VDD), LED6.1 (VDD), LED7.1 (VDD), LED8.1 (VDD), LED9.1 (VDD), LED10.1 (VDD), LED11.1 (VDD), LED12.1 (VDD), LED13.1 (VDD), LED14.1 (VDD), LED15.1 (VDD), LED16.1 (VDD), LED17.1 (VDD), LED18.1 (VDD), LED19.1 (VDD), LED20.1 (VDD), LED21.1 (VDD), LED22.1 (VDD), LED23.1 (VDD), LED24.1 (VDD), LED25.1 (VDD), LED26.1 (VDD), LED27.1 (VDD), LED28.1 (VDD), LED29.1 (VDD), LED30.1 (VDD), LED31.1 (VDD), LED32.1 (VDD), LED33.1 (VDD), LED34.1 (VDD), LED35.1 (VDD), LED36.1 (VDD), LED37.1 (VDD), LED38.1 (VDD), LED39.1 (VDD), LED40.1 (VDD), LED41.1 (VDD), LED42.1 (VDD), LED43.1 (VDD), LED44.1 (VDD), LED45.1 (VDD), LED46.1 (VDD), LED47.1 (VDD), LED48.1 (VDD), LED49.1 (VDD), LED50.1 (VDD), LED51.1 (VDD), LED52.1 (VDD), LED53.1 (VDD), LED54.1 (VDD), LED55.1 (VDD), LED56.1 (VDD), LED57.1 (VDD), LED58.1 (VDD), LED59.1 (VDD), LED60.1 (VDD), LED61.1 (VDD), LED62.1 (VDD), LED63.1 (VDD), LED64.1 (VDD), OL1.3 (VCC), U6.5 (VCC)

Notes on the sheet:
L_SHIFT
KEYBOARD INTERFACE
A10 TO RGB LED STRAND
SPACE
OLED
FRAM AND FLASH
ENTER
RGB STRAND
L_CTRL
ESC
CRYSTAL
FN_2
MCU
FN_1
ROTARY ENCODER
MOUNTING HOLES
BOOT1
BOOT
1mm square pads on back
The GarlicBoard 2
5V to drive WS2812
R_SHIFT
L_ALT
PAD LOCK
PERIOD
TAB
R_CTRL
BCK SPC
EMERGENCY PADS
SWITCH MATRIX
USB CONNECTOR AND ESD
RETURN
TO RGB STRAND
R_CMD
POWER SUPPLY
R_ALT
RESET CIRCUIT
May 1, 2022
L_CMD

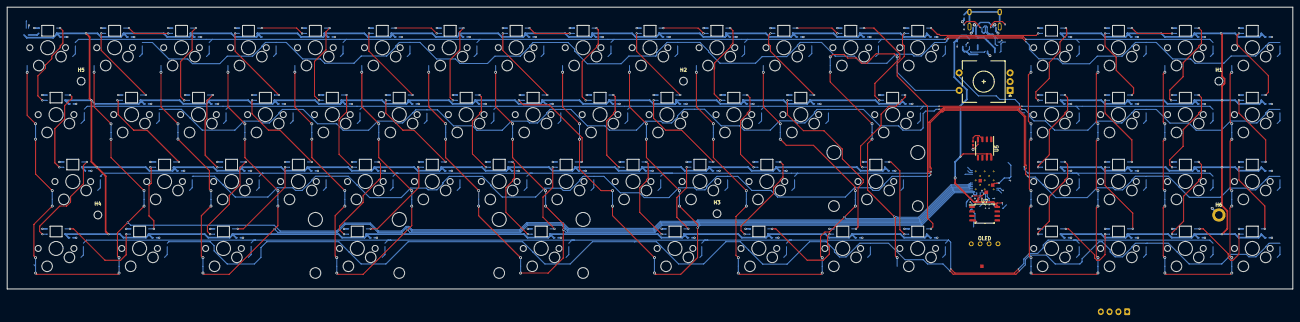
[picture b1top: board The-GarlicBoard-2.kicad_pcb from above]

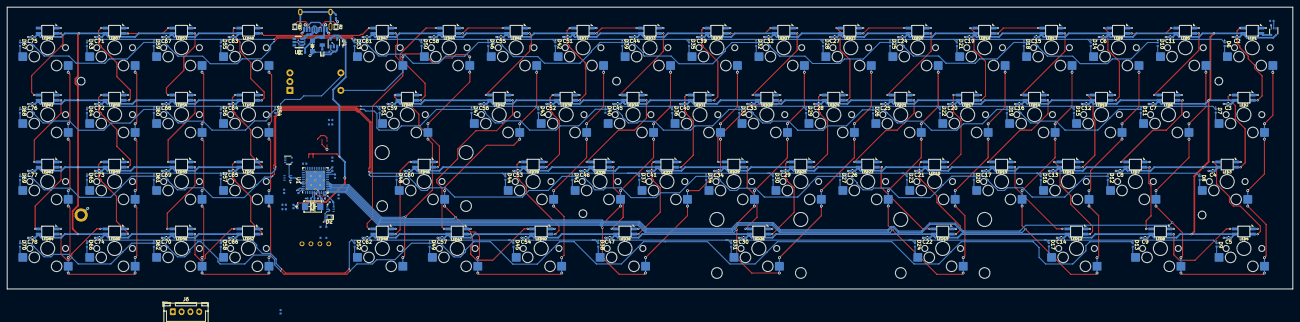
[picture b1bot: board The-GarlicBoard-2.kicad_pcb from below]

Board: 2 copper layers, 365.9 x 80.2 mm, 314 parts (234 on the bottom side), 186 nets.

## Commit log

2022-04-29 Initialize project
2022-04-29 Add submodules
2022-04-29 Add footprint libraries
2022-04-30 Initial schematic set up
2022-04-30 More schematic updates, added three LDO options
2022-05-02 Updated mainboard schematic
2022-05-02 Cleaned up libraries
2022-05-02 Cleaned up files
2022-05-02 More schematic updates
2023-01-02 Update
    Update
2023-01-02 First Major Update of 2023
    Major updates to schematics and first revisions of PCB layout
2023-01-02 Removed Backup files
2023-01-03 Wiring in USB and MCU
2023-01-03 Removed excess backups
2023-01-05 Final Updates
2023-01-05 Added corners to PCB
2023-01-11 Conversion from STM32 to RP2040
    Removed STM32 MCU and replace with RP2040. Full rewire of board.
2023-01-12 Updated USB circuitry
2023-01-12 Revision update
    Removed USB connector and related components in favor of using Unified Daughterboard C3. Added 3D models to the footprints. Added JST connector for connecting to UD C3.
2023-01-16 Rotated clock, trimmed edge cuts
2023-02-13 Increased copper to copper tolerance to .2mm
2023-02-13 Slight tweaks
2023-02-16 Final additions and tweaks
2023-02-23 Updated components
    Added reverse polarity protection and debug LED
2023-02-23 Corrected Silkscreen typo
2023-03-22 Final update
2023-03-29 Simple changes
